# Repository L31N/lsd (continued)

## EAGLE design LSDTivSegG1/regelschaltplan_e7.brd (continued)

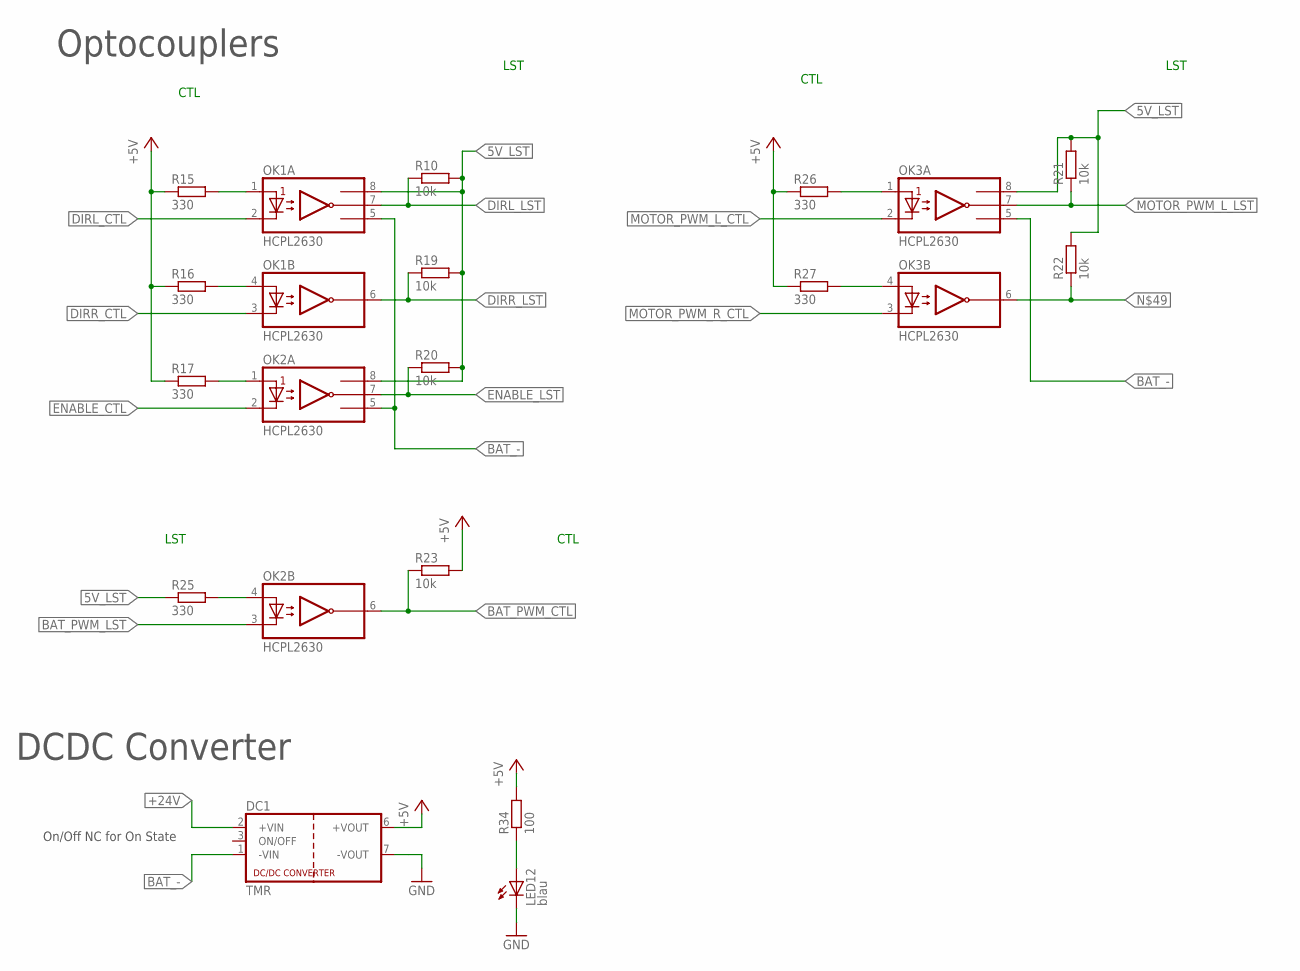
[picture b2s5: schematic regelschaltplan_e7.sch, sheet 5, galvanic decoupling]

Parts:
DC1: TMR; TRACO_SIP-8
LED12: blau; LED3MM
OK1, OK2, OK3: HCPL2630; DIL08
R10, R19, R20, R21, R22, R23: 10k; 0207/10
R15, R16, R17, R25, R26, R27: 330; 0207/10
R34: 100; 0207/10

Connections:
5V_LST: OK1.8 (VCC), OK2.8 (VCC), OK3.8 (VCC), R10.2, R19.2, R20.2, R21.2, R22.2, R25.1; also elsewhere on the board
+24V: DC1.2 (+VIN); also elsewhere on the board
BAT_-: DC1.1 (-VIN), OK1.5 (GND), OK2.5 (GND), OK3.5 (GND); also elsewhere on the board
BAT_PWM_CTL: OK2.6 (VO2), R23.1; also elsewhere on the board
BAT_PWM_LST: OK2.3 (C2); also elsewhere on the board
DIRL_CTL: OK1.2 (C1); also elsewhere on the board
DIRL_LST: OK1.7 (VO1), R10.1; also elsewhere on the board
DIRR_CTL: OK1.3 (C2); also elsewhere on the board
DIRR_LST: OK1.6 (VO2), R19.1; also elsewhere on the board
ENABLE_CTL: OK2.2 (C1); also elsewhere on the board
ENABLE_LST: OK2.7 (VO1), R20.1; also elsewhere on the board
GND: DC1.7 (-VOUT), LED12.K (C); also elsewhere on the board
MOTOR_PWM_L_CTL: OK3.2 (C1); also elsewhere on the board
MOTOR_PWM_L_LST: OK3.7 (VO1), R21.1; also elsewhere on the board
MOTOR_PWM_R_CTL: OK3.3 (C2); also elsewhere on the board
unnamed 58: DC1.6 (+VOUT), R15.1, R16.1, R17.1, R23.2, R26.1, R27.1, R34.2; also elsewhere on the board
unnamed: OK1.1 (A1), R15.2
unnamed: OK1.4 (A2), R16.2
unnamed: OK2.1 (A1), R17.2
unnamed: OK2.4 (A2), R25.2
unnamed: OK3.4 (A2), R27.2
unnamed: OK3.1 (A1), R26.2
unnamed: LED12.A, R34.1
unnamed 71: OK3.6 (VO2), R22.1; also elsewhere on the board

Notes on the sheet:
DCDC Converter
On/Off NC for On State
Optocouplers
LST
CTL

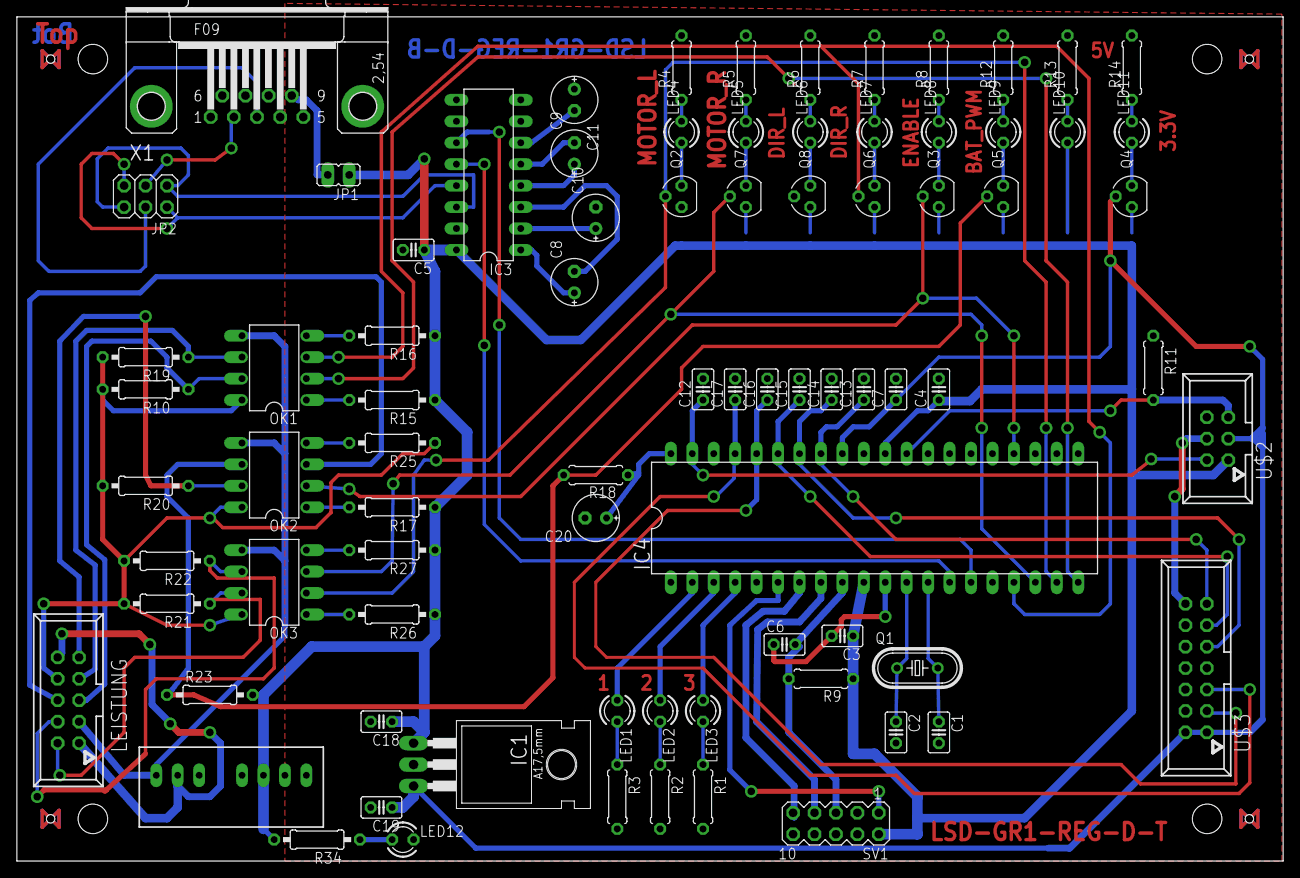
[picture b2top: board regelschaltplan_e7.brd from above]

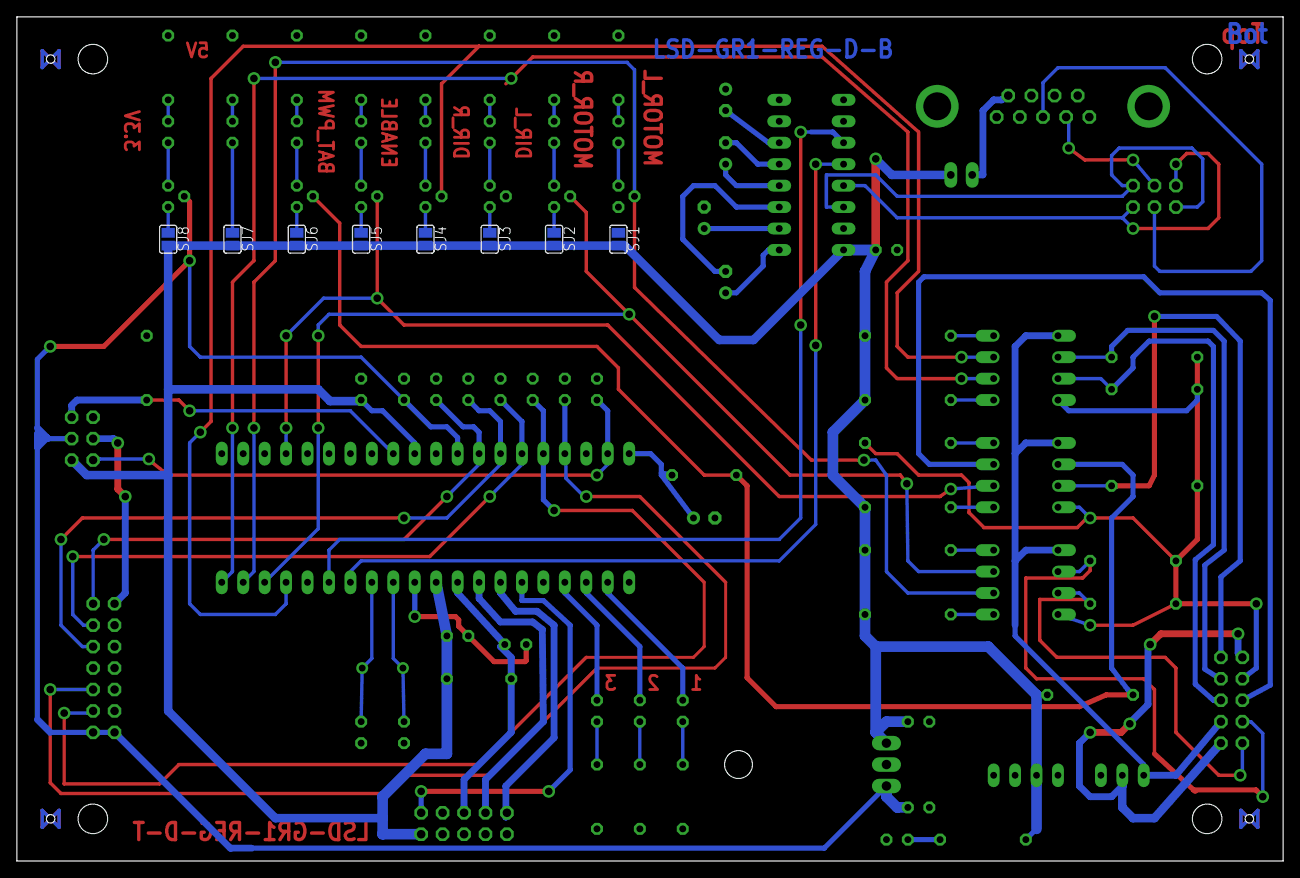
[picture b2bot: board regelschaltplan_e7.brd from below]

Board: 2 copper layers, 150.0 x 100.0 mm, 90 parts (8 on the bottom side), 81 nets.

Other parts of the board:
U$1: BOARD

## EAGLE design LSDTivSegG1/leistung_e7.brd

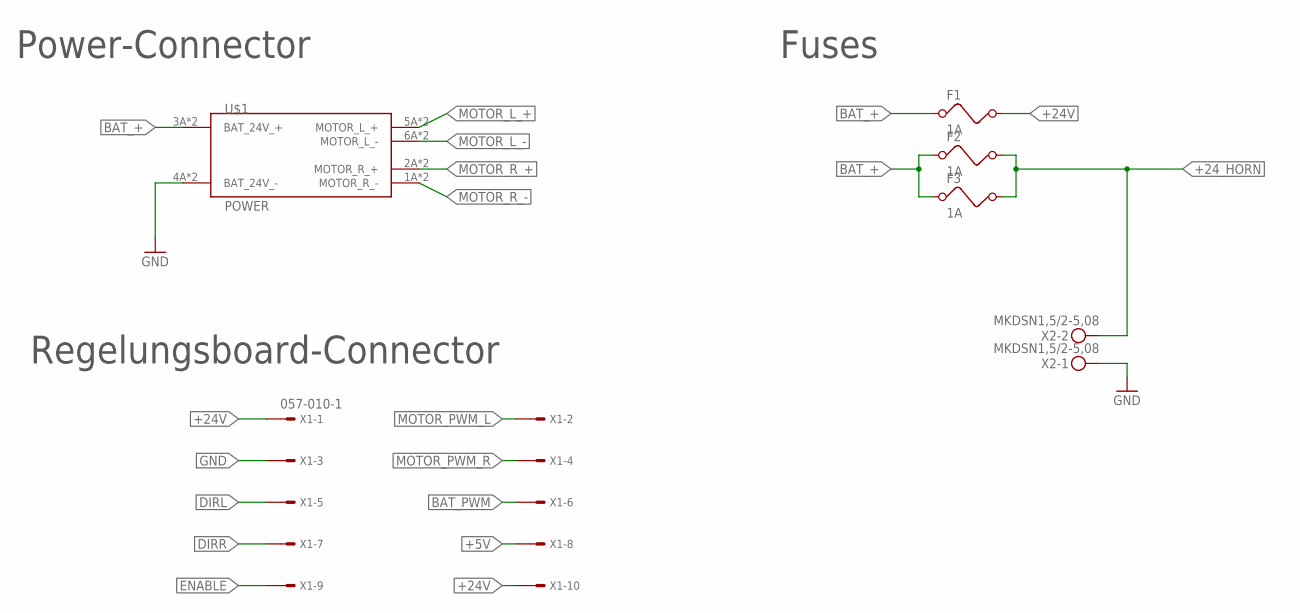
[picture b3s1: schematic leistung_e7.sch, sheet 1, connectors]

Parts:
F1, F2, F3: 1A; FUSE
U$1: POWER; CON_POWER
X1: 057-010-1
X2: MKDSN1,5/2-5,08

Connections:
+5V: X1.8; also elsewhere on the board
+24V: F1.2, X1.1, X1.10; also elsewhere on the board
+24_HORN: F2.2, F3.2, X2.2
BAT_+: F1.1, F2.1, F3.1, U$1.3A (BAT_24V_+), U$1.3B (BAT_24V_+); also elsewhere on the board
BAT_PWM: X1.6; also elsewhere on the board
DIRL: X1.5; also elsewhere on the board
DIRR: X1.7; also elsewhere on the board
ENABLE: X1.9; also elsewhere on the board
GND: U$1.4A (BAT_24V_-), U$1.4B (BAT_24V_-), X1.3, X2.1; also elsewhere on the board
MOTOR_L_+: U$1.5A (MOTOR_L_+), U$1.5B (MOTOR_L_+); also elsewhere on the board
MOTOR_L_-: U$1.6A (MOTOR_L_-), U$1.6B (MOTOR_L_-); also elsewhere on the board
MOTOR_PWM_L: X1.2; also elsewhere on the board
MOTOR_PWM_R: X1.4; also elsewhere on the board
MOTOR_R_+: U$1.2A (MOTOR_R_+), U$1.2B (MOTOR_R_+); also elsewhere on the board
MOTOR_R_-: U$1.1A (MOTOR_R_-), U$1.1B (MOTOR_R_-); also elsewhere on the board

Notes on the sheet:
Power-Connector
Regelungsboard-Connector
Fuses

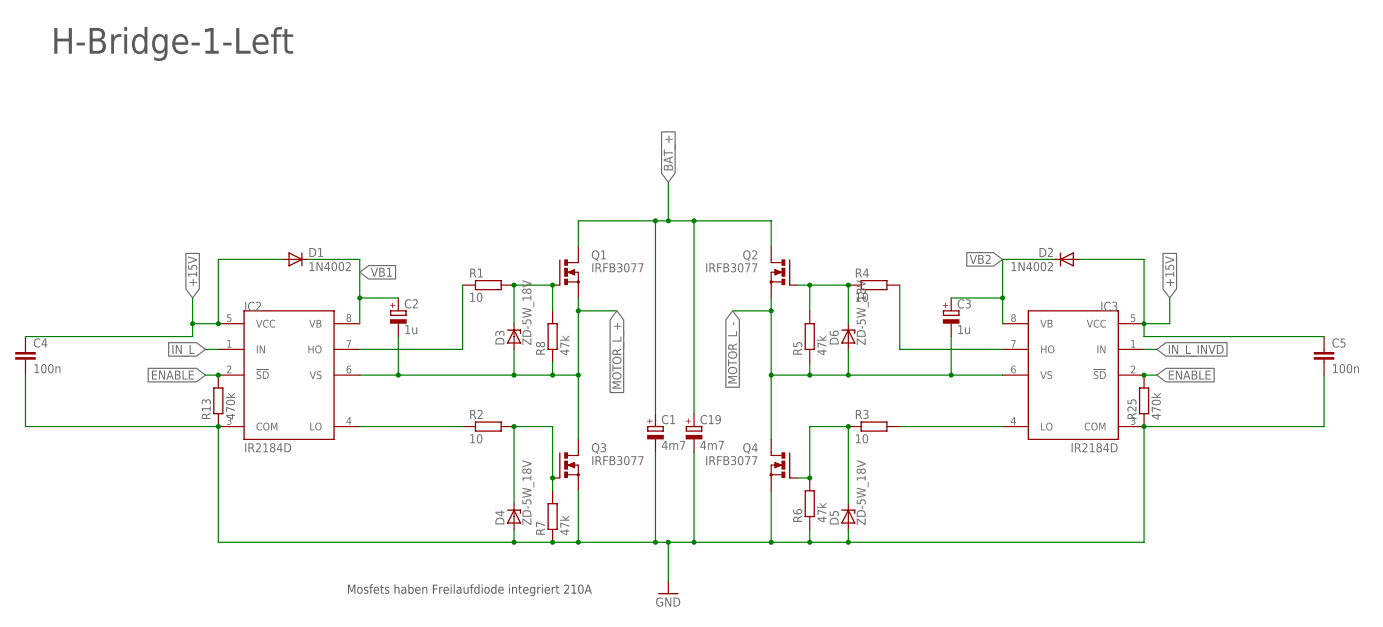
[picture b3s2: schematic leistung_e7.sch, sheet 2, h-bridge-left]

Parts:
C1, C19: 4m7; E7,5-18
C2, C3: 1u; E2,5-5
C4, C5: 100n; C025-025X050
D1, D2: 1N4002; DO41-10
D3, D4, D5, D6: ZD-5W_18V; ZDIO-10
IC2, IC3: IR2184D; DIL08
Q1, Q2, Q3, Q4: IRFB3077; TO220BV
R1, R2, R3, R4: 10; 0207/7
R5, R6, R7, R8: 47k; 0207/7
R13, R25: 470k; 0207/7

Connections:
+15V: C4.1, C5.1, D1.A, D2.A, IC2.5 (VCC), IC3.5 (VCC); also elsewhere on the board
BAT_+: C1.+, C19.+, Q1.D, Q2.D; also elsewhere on the board
ENABLE: IC2.2 (!SD), IC3.2 (!SD), R13.2, R25.2; also elsewhere on the board
GND: C1.-, C4.2, C5.2, C19.-, D4.A, D5.A, IC2.3 (COM), IC3.3 (COM), Q3.S, Q4.S, R6.1, R7.1, R13.1, R25.1; also elsewhere on the board
IN_L: IC2.1 (IN); also elsewhere on the board
IN_L_INVD: IC3.1 (IN); also elsewhere on the board
MOTOR_L_+: C2.-, D3.A, IC2.6 (VS), Q1.S, Q3.D, R8.1; also elsewhere on the board
MOTOR_L_-: C3.-, D6.A, IC3.6 (VS), Q2.S, Q4.D, R5.1; also elsewhere on the board
unnamed: D4.C, Q3.G, R2.2, R7.2
unnamed: D3.C, Q1.G, R1.2, R8.2
unnamed: D6.C, Q2.G, R4.1, R5.2
unnamed: D5.C, Q4.G, R3.1, R6.2
unnamed: IC2.4 (LO), R2.1
unnamed: IC2.7 (HO), R1.1
unnamed: IC3.7 (HO), R4.2
unnamed: IC3.4 (LO), R3.2
VB1: C2.+, D1.C, IC2.8 (VB)
VB2: C3.+, D2.C, IC3.8 (VB)

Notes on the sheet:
H-Bridge-1-Left
Mosfets haben Freilaufdiode integriert 210A

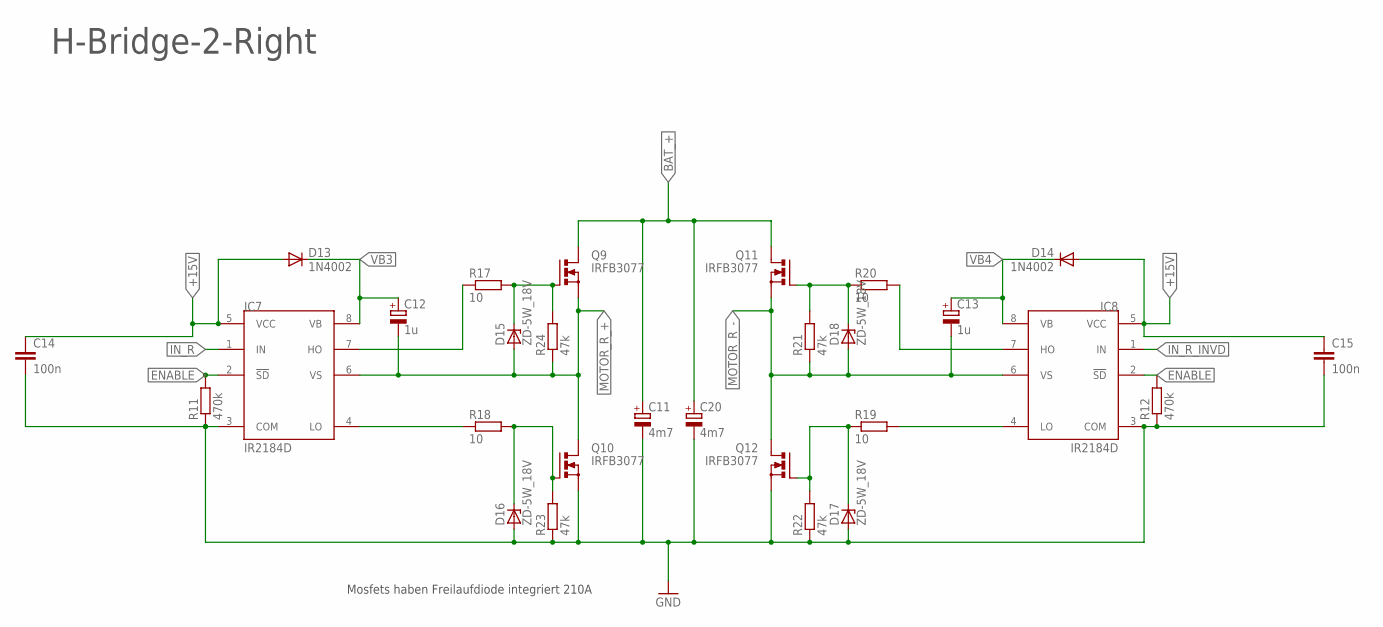
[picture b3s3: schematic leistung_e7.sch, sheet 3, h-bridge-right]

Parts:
C11, C20: 4m7; E7,5-18
C12, C13: 1u; E2,5-5
C14, C15: 100n; C025-025X050
D13, D14: 1N4002; DO41-10
D15, D16, D17, D18: ZD-5W_18V; ZDIO-10
IC7, IC8: IR2184D; DIL08
Q9, Q10, Q11, Q12: IRFB3077; TO220BV
R11, R12: 470k; 0207/7
R17, R18, R19, R20: 10; 0207/7
R21, R22, R23, R24: 47k; 0207/7

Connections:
+15V: C14.1, C15.1, D13.A, D14.A, IC7.5 (VCC), IC8.5 (VCC); also elsewhere on the board
BAT_+: C11.+, C20.+, Q9.D, Q11.D; also elsewhere on the board
ENABLE: IC7.2 (!SD), IC8.2 (!SD), R11.2, R12.2; also elsewhere on the board
GND: C11.-, C14.2, C15.2, C20.-, D16.A, D17.A, IC7.3 (COM), IC8.3 (COM), Q10.S, Q12.S, R11.1, R12.1, R22.1, R23.1; also elsewhere on the board
IN_R: IC7.1 (IN); also elsewhere on the board
IN_R_INVD: IC8.1 (IN); also elsewhere on the board
MOTOR_R_+: C12.-, D15.A, IC7.6 (VS), Q9.S, Q10.D, R24.1; also elsewhere on the board
MOTOR_R_-: C13.-, D18.A, IC8.6 (VS), Q11.S, Q12.D, R21.1; also elsewhere on the board
unnamed: D16.C, Q10.G, R18.2, R23.2
unnamed: D15.C, Q9.G, R17.2, R24.2
unnamed: D18.C, Q11.G, R20.1, R21.2
unnamed: D17.C, Q12.G, R19.1, R22.2
unnamed: IC7.4 (LO), R18.1
unnamed: IC7.7 (HO), R17.1
unnamed: IC8.7 (HO), R20.2
unnamed: IC8.4 (LO), R19.2
VB3: C12.+, D13.C, IC7.8 (VB)
VB4: C13.+, D14.C, IC8.8 (VB)

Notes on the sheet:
H-Bridge-2-Right
Mosfets haben Freilaufdiode integriert 210A

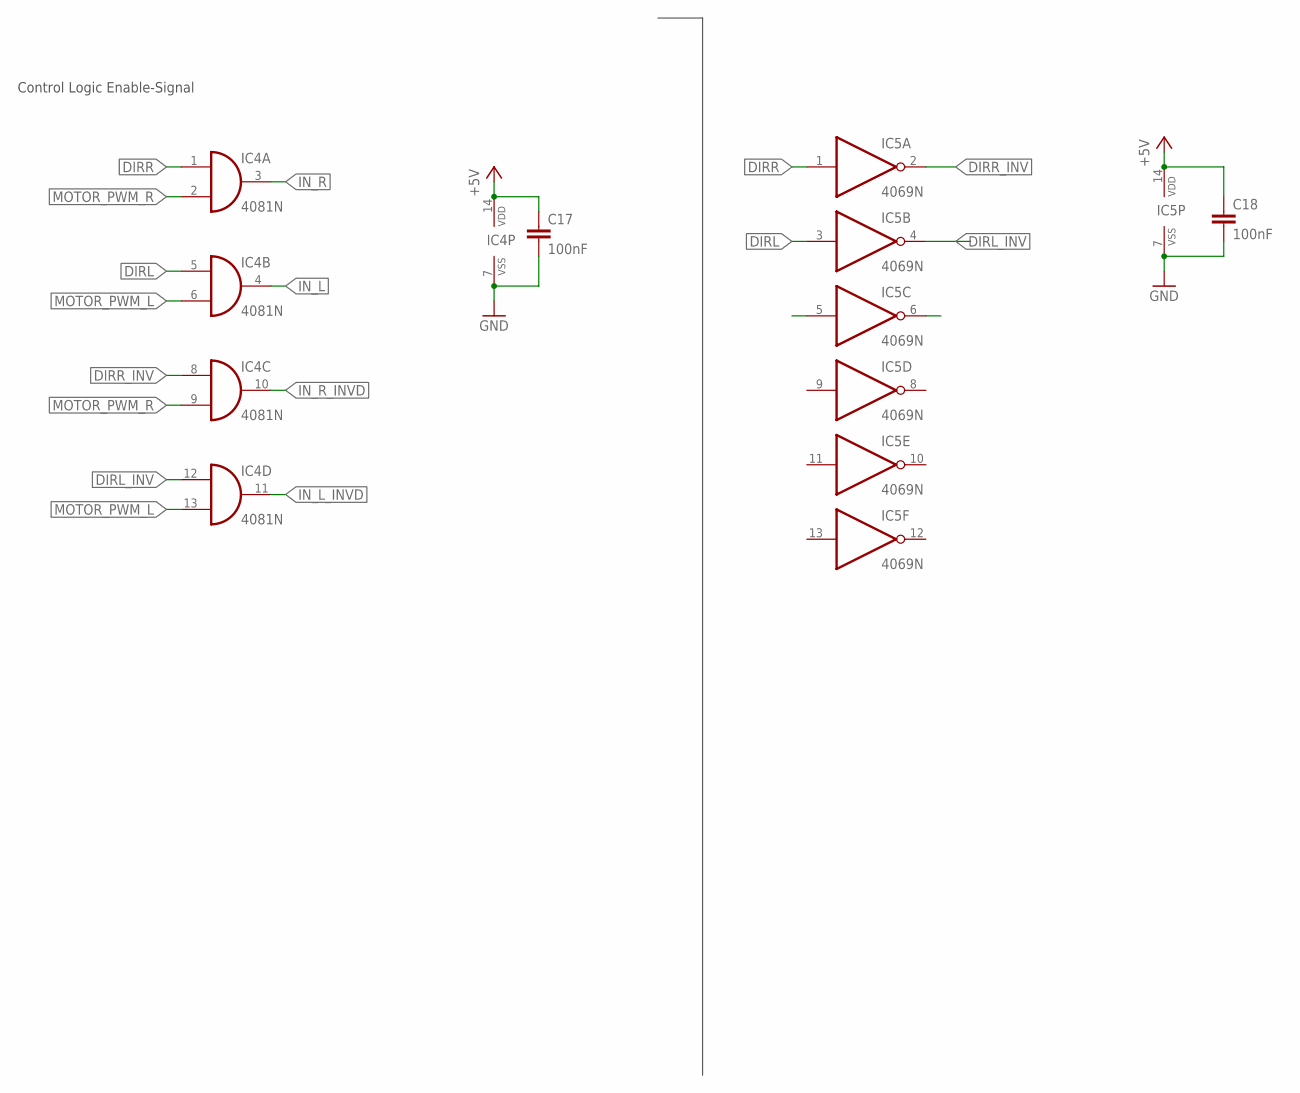
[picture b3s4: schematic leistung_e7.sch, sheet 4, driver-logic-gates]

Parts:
C17, C18: 100nF; C025-025X050
IC4: 4081N; DIL14
IC5: 4069N; DIL14

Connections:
+5V: C17.1, C18.1, IC4.14 (VDD), IC5.14 (VDD); also elsewhere on the board
DIRL: IC4.5 (I0), IC5.3 (I); also elsewhere on the board
DIRL_INV: IC4.12 (I0), IC5.4 (O)
DIRR: IC4.1 (I0), IC5.1 (I); also elsewhere on the board
DIRR_INV: IC4.8 (I0), IC5.2 (O)
GND: C17.2, C18.2, IC4.7 (VSS), IC5.7 (VSS); also elsewhere on the board
IN_L: IC4.4 (O); also elsewhere on the board
IN_L_INVD: IC4.11 (O); also elsewhere on the board
IN_R: IC4.3 (O); also elsewhere on the board
IN_R_INVD: IC4.10 (O); also elsewhere on the board
MOTOR_PWM_L: IC4.6 (I1), IC4.13 (I1); also elsewhere on the board
MOTOR_PWM_R: IC4.2 (I1), IC4.9 (I1); also elsewhere on the board

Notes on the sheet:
Control Logic Enable-Signal

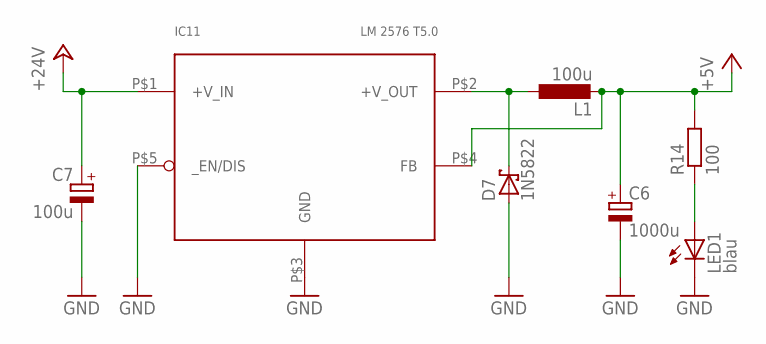
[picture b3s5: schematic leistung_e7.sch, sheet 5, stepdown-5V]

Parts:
C6: 1000u; E5-13
C7: 100u; E2,5-4R
D7: 1N5822; CB417-15
IC11: LM 2576 T5.0; TO220-5_STAGGERED
L1: 100u; 0207/10
LED1: blau; LED3MM
R14: 100; 0207/10

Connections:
+5V: C6.+, IC11.P$4 (FB), L1.2, R14.2; also elsewhere on the board
+24V: C7.+, IC11.P$1 (+V_IN); also elsewhere on the board
GND: C6.-, C7.-, D7.A, IC11.P$3 (GND), IC11.P$5 (_EN/DIS), LED1.K (C); also elsewhere on the board
unnamed: D7.C, IC11.P$2 (+V_OUT), L1.1
unnamed: LED1.A, R14.1

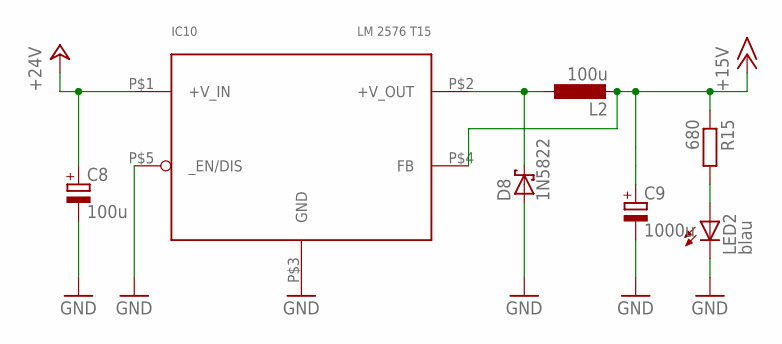
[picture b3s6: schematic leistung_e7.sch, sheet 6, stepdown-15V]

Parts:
C8: 100u; E2,5-7
C9: 1000u; E5-13
D8: 1N5822; CB429-15
IC10: LM 2576 T15; TO220-5_STAGGERED
L2: 100u; 0207/10
LED2: blau; LED3MM
R15: 680; 0207/10

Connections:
+15V: C9.+, IC10.P$4 (FB), L2.2, R15.1; also elsewhere on the board
+24V: C8.+, IC10.P$1 (+V_IN); also elsewhere on the board
GND: C8.-, C9.-, D8.A, IC10.P$3 (GND), IC10.P$5 (_EN/DIS), LED2.K (C); also elsewhere on the board
unnamed: LED2.A, R15.2
unnamed: D8.C, IC10.P$2 (+V_OUT), L2.1

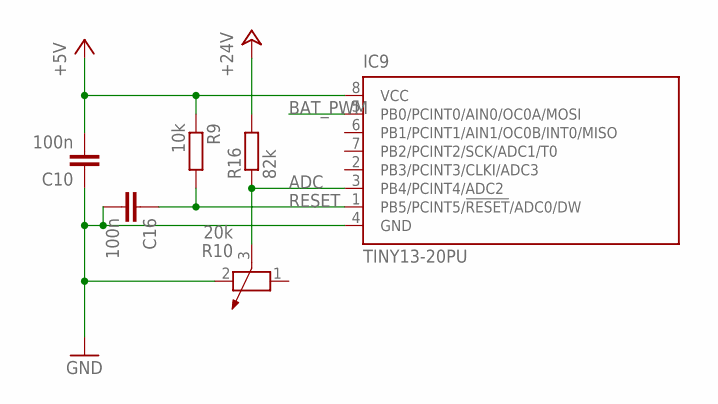
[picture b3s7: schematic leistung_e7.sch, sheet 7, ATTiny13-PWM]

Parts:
C10, C16: 100n; C025-025X050
IC9: TINY13-20PU; DIL08
R9: 10k; 0207/10
R10: 20k; PT-10
R16: 82k; 0207/10

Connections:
+5V: C10.2, IC9.8 (VCC), R9.1; also elsewhere on the board
+24V: R16.2; also elsewhere on the board
ADC: IC9.3 (PB4/PCINT4/ADC2), R10.3, R16.1
BAT_PWM: IC9.5 (PB0/PCINT0/AIN0/OC0A/MOSI); also elsewhere on the board
GND: C10.1, C16.2, IC9.4 (GND), R10.2; also elsewhere on the board
RESET: C16.1, IC9.1 (PB5/PCINT5/!RESET!/ADC0/DW), R9.2

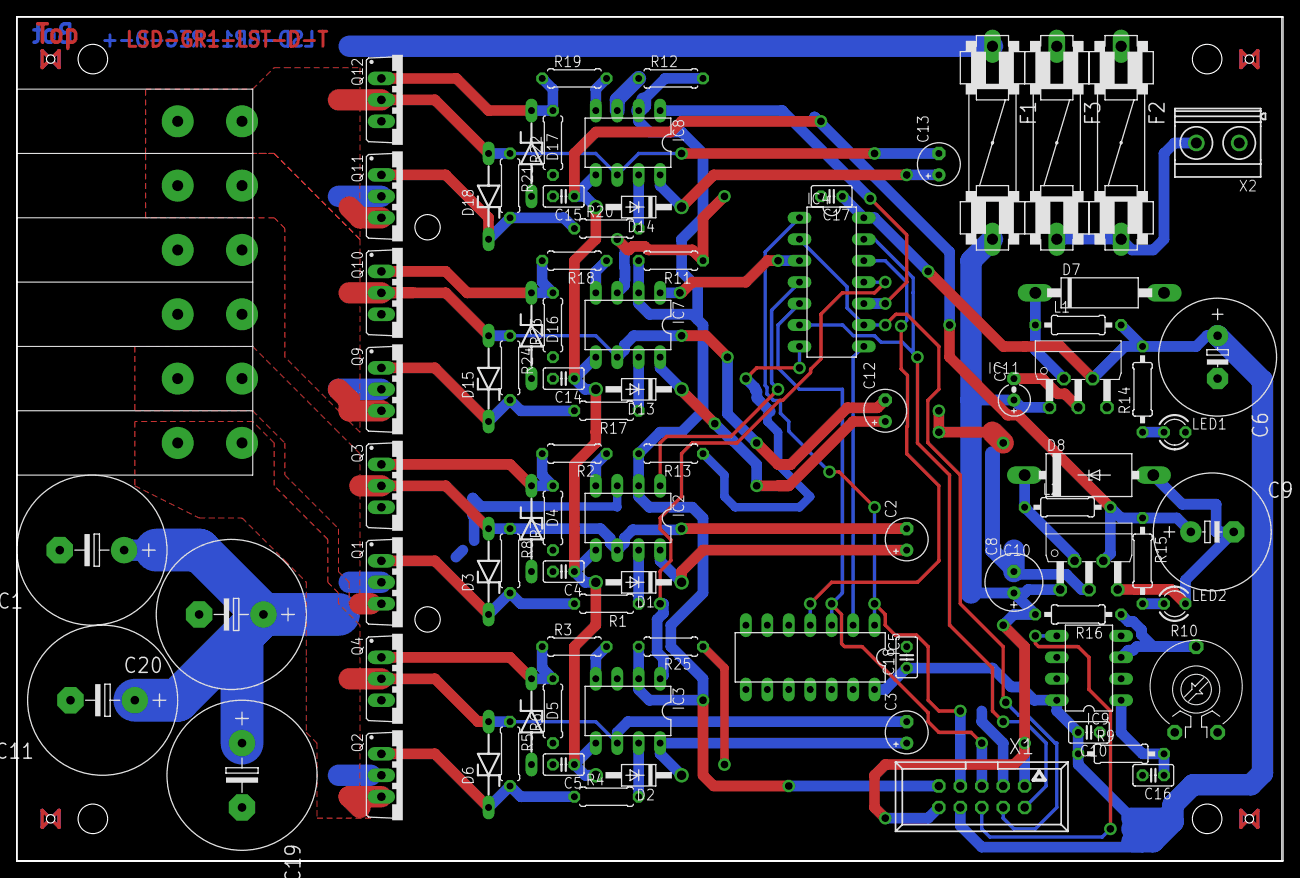
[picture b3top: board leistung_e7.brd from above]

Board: 2 copper layers, 150.0 x 100.0 mm, 87 parts (0 on the bottom side), 48 nets.

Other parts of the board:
U$2: BOARD

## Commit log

2018-09-28 added datasheet for power mosfet motor driver
2018-09-28 addet readme
2018-09-28 created new empty eagle project
2018-09-28 renamed readme file
2018-09-28 Added Draw IO drawings
2018-09-28 added .gitignore file for eagle projects
2018-09-28 added lsd library added schematic for display board -> containing connector, atmega8, rs232, buttons
2018-09-28 first complete schematic version
2018-09-28 changed resistor packages on sheet 1
2018-09-28 exported schematic as PDF
2018-09-28 Added files from Drive X
2018-09-28 Updated to newest state
2018-09-30 added Leistungsschaltplan
2018-10-01 added values for all the parts in schematic added some datasheets
2018-10-01 merged with regelungsplatine
2018-10-01 edit device lf33ab to lib
2018-10-01 developed hard
2018-10-01 added ltv844 to library
2018-10-01 added reichelt directory with the order information for display board
2018-10-01 changed naming high/low voltage area
2018-10-01 added frames to display schematic
2018-10-01 added supply to logic gates
2018-10-01 edit new schaltplan
2018-10-01 merged alexs schmeatic with the one from dominik
2018-10-01 added 5V status led to LST side
2018-10-01 added jumper to interrupt VCC via RS232 to debug
2018-10-01 added jumper to rs232 connector to interrupt 5V supply
2018-10-02 added libreoffice gitignore
2018-10-02 moved decoupling to regelungsplatine
2018-10-02 exported pdf file of the schematics
2018-10-02 replaced resistor with potentiometer in voltage devider for battery monitoring
2018-10-02 added blocking capacitors to 3V3 supply added rs323 cross pinhead
2018-10-02 fixed mirrored isp connector in display board
2018-10-02 exported versions for eagle 7.x.x
2018-10-02 added RS232 crossing pinhead
2018-10-02 added supply pins to max232
2018-10-02 added blocking capacities to IO-Expanders
2018-10-02 updated display contrast trimming circuit
2018-10-02 added display board frame to library replaced board frame in display schematic
2018-10-02 edit optokoppler with hpcl2621
2018-10-02 added values to PCF blocking capacities
2018-10-02 Nachbesprechung Änderungen gemacht
2018-10-02 final changes and bestückungsliste
2018-10-02 fixed some bugs in schematic board file with all components placed
2018-10-02 aktueller schaltplan
2018-10-02 eagle 7 export
2018-10-02 worked on regelschaltplan
2018-10-02 exported the current version of the eagle 7 compatible file for display board
2018-10-02 working on display.brd
2018-10-03 worked on board layout (ca. 80% routed) changed LEDs from GND to +5V
2018-10-03 added npn transistors to LED bars
2018-10-03 routed led transistors
2018-10-03 fixed wrong naming of SCL (used SDL) for IO-Expanders
2018-10-03 worked on dispaly.brd, only some airwire left
2018-10-03 finished routing there just some wire stubs to remove (DRC)
2018-10-04 removed wire stub drc warnings, increased wire width for +5V
2018-10-04 added layer lables
2018-10-04 changed layer label size
2018-10-04 layouted H-Bridges
2018-10-04 added pullup resistors to buttons
2018-10-04 added values to the pullups (buttons)
2018-10-04 changed routing of the +5V to pullups, away from pcb border
2018-10-04 edit regelungsboard-fertig
2018-10-04 finalized board
2018-10-04 saved again
2018-10-05 push of bennis files
2018-10-05 added Text on Layers for identification
2018-10-05 added Text
2018-10-05 saved as e7 for benni
2018-10-05 edit regellayout done
2018-10-05 updated eagle7 copatible exports of display and leistung boards
2018-10-05 removed drillings from display_frame in library
2018-10-05 fixed alle clearance error (for bigger pads (12mil))
2018-10-05 fixes aus der Nachbesprechung
2018-10-05 used isolation 20 for ground planes
2018-10-05 fixed some only top layer gnd connections
2018-10-05 exported e7 compatible files of current version
2018-10-08 edit regelschaltplan_e7 bauteil fixed
2018-10-08 updated e7 compatible version of display
2018-10-08 exported pdf of the board files
2018-10-08 updated display.bom
